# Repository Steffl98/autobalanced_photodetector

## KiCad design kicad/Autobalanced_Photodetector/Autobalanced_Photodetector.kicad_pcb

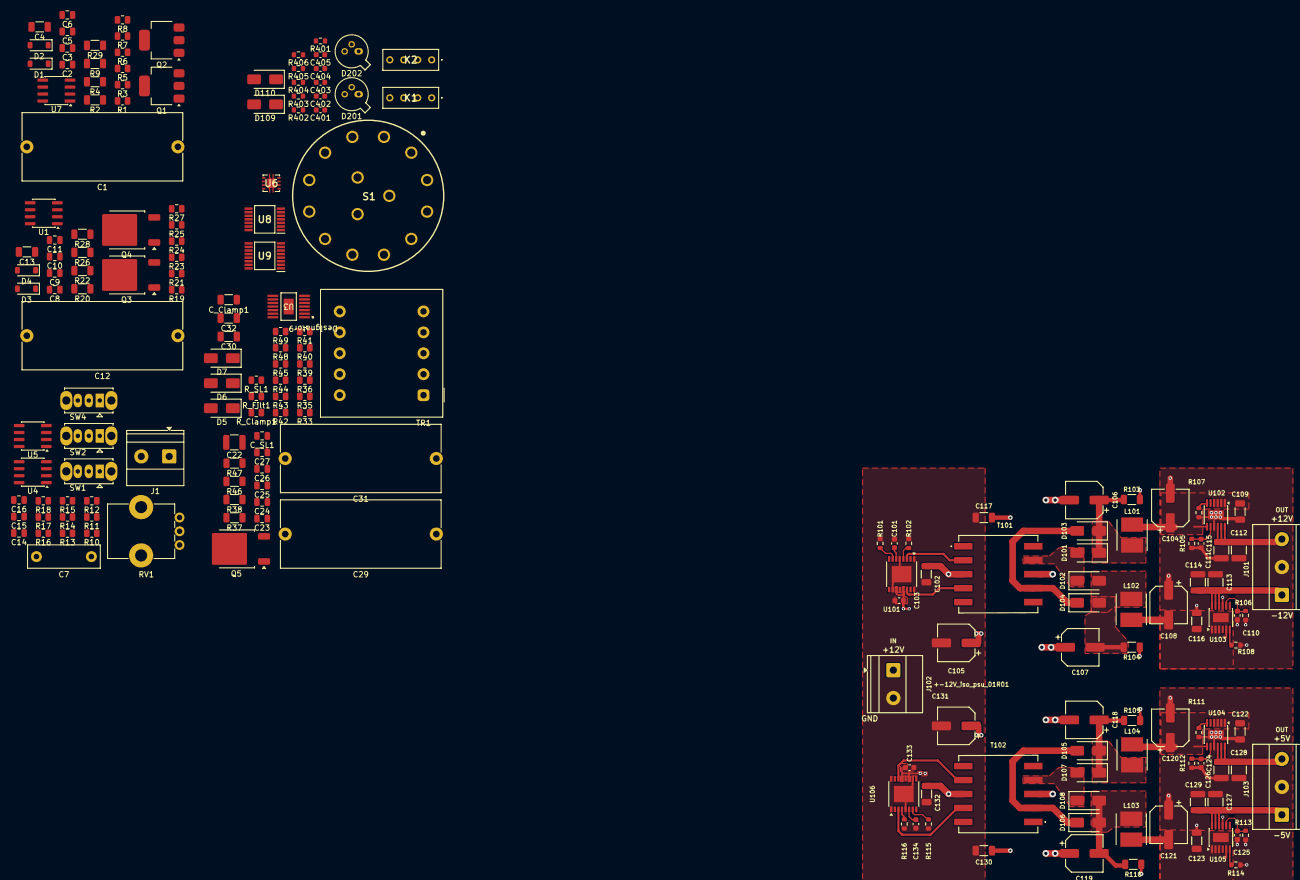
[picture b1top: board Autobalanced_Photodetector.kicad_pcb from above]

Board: 2 copper layers, 193 parts (0 on the bottom side), 117 nets.

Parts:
C1, C12, C29, C31: 3.3u; C_Rect_L29.0mm_W12.2mm_P27.50mm_MKT
C2, C11: 15n; C_0805_2012Metric
C3, C5, C6, C8, C9, C10, C14, C15, C16, C23, C24: 100n; C_0805_2012Metric
C4, C13, C30, C32: 10n; C_1206_3216Metric
C7: 1u; C_Rect_L13.0mm_W4.0mm_P10.00mm_FKS3_FKP3_MKS4
C22: 22u; C_1210_3225Metric
C25: 2.2u; C_0805_2012Metric
C26: 4.7u; C_0805_2012Metric
C27: 4.7n; C_0805_2012Metric
C101, C134: 680pF; C_0603_1608Metric
C102, C109, C116, C117, C122, C123, C130, C132: 4.7u; C_1206_3216Metric
C103, C133: 100nF; C_0603_1608Metric
C104, C108, C120, C121: 47uF; CP_Elec_6.3x5.8
C105, C106, C107, C118, C119, C131: 100uF; CP_Elec_6.3x7.7
C110, C115, C124, C125: 4.7uF; C_0603_1608Metric
C111, C112, C113, C114, C126, C127, C128, C129: 22uF; C_1210_3225Metric
C401: 10n; C_0603_1608Metric
C402: 7.5n; C_0603_1608Metric
C403: 470p; C_0603_1608Metric
C404: 10p; C_0603_1608Metric
C405: 100n; C_0603_1608Metric
C_Clamp1: 4.7n; C_1206_3216Metric
C_SL1: 100p; C_0805_2012Metric
D1, D2, D3, D4: MMSZ5242B-E3-08; D_SOD-123
D5: MER3DMA-AU_R2_006A1; D_SMA
D6, D7: STTH1R06A; D_SMA
D101, D102, D103, D104, D105, D106, D107, D108, D109, D110: STPS1L60A; D_SMA
D201, D202: Photodiode_TO18; TO-18-3_Window
J1: Conn_01x02; TerminalBlock_Phoenix_MKDS-1,5-2-5.08_1x02_P5.08mm_Horizont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
J101, J103: Screw_Terminal_01x03; TerminalBlock_Phoenix_MKDS-1,5-3-5.08_1x03_P5.08mm_Horizont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
J102: Screw_Terminal_01x02; TerminalBlock_Phoenix_MKDS-1,5-2-5.08_1x02_P5.08mm_Horizont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
K1, K2: 9012-12-10; 90121210
L101, L102, L103, L104: 33uH; L_TDK_VLS5030EX
Q1, Q2: STN1NK60Z; SOT-223
Q3, Q4: FQD2P40TM; TO-252-2
Q5: IPD5N25S3-430; TO-252-2
R1, R23, R43: 10; R_0805_2012Metric
R2, R9, R20, R22: 120k; R_1206_3216Metric
R3, R14, R16, R17, R18, R21: 10k; R_0805_2012Metric
R4, R26, R28, R29: 680k; R_1206_3216Metric
R5, R6, R7, R24, R25, R27: 47k; R_0805_2012Metric
R8, R10, R19, R35: 1k; R_0805_2012Metric
R11: 4.7k; R_0805_2012Metric
R12: 470k; R_0805_2012Metric
R13, R15, R44: 100k; R_0805_2012Metric
R33: 0.1; R_0805_2012Metric
R36, R49: 100; R_0805_2012Metric
R37, R38, R46, R47: 220k; R_1206_3216Metric
R39, R48: 1.8k; R_0805_2012Metric
R40: 680k; R_0805_2012Metric
R41: 120k; R_0805_2012Metric
R42: 20k; R_0805_2012Metric
R45: 150k; R_0805_2012Metric
R101, R102, R115, R116: 16.9k; R_0603_1608Metric
R103, R104, R109, R110: 5k; R_1206_3216Metric
R105, R106: 120k; R_0603_1608Metric
R107, R404: 1k; R_0603_1608Metric
R108: 24.9k; R_0603_1608Metric
R111: 1.5k; R_0603_1608Metric
R112, R113: 49.9k; R_0603_1608Metric
R114: 37.4k; R_0603_1608Metric
R401: 15.9k; R_0603_1608Metric
R402, R403: 100k; R_0603_1608Metric
R405, R406: 10k; R_0603_1608Metric
RV1: R_Potentiometer; Potentiometer_Bourns_PTV09A-1_Single_Vertical
R_Clamp1: 18k; R_0805_2012Metric
R_Filt1: 100; R_0805_2012Metric
R_SL1: 2200; R_0805_2012Metric
S1: CK1051
SW1, SW2, SW4: SW_SPDT; SW_Slide_SPDT_Straight_CK_OS102011MS2Q
T101, T102: CTX02-16076; CTX0216076
TR1: Wuerth 750311681C enter-Tapped; Transformer_Wuerth_750343373
U1, U4, U5, U7: OPA2992IDR; SOIC-8_3.9x4.9mm_P1.27mm
U3: LM5156HPWPR; PWP0014H-IPC_A
U6: OPA659IDRBT; OPA659_DRB
U8: OPA4192IPWR; SOP65P640X120-14N
U9: TMUX6136PWR; SOP65P640X120-16N
U101, U106: LT3439; TSSOP-16-1EP_4.4x5mm_P0.65mm
U102, U104: LT3045xMSE; MSOP-12-1EP_3x4.039mm_P0.65mm_EP1.651x2.845mm
U103, U105: LT3094xMSE; MSOP-12-1EP_3x4.039mm_P0.65mm_EP1.651x2.845mm

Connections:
/Flyback/HV_RAW_NEG: C29.2, C30.2, D7.2 (A), R20.1, R23.1, R46.1
/Flyback/HV_RAW_POS: C31.1, C32.1, D6.1 (K), R1.1, R9.1, R37.1
/HV_Regulator_Neg/HV_BIAS_NEG: C12.1, C13.1, D4.1 (K), D202.3 (A), Q4.3 (S), R28.1
/HV_Regulator_Neg/V_REF_NEG: R17.2, R25.2, U5.7
/HV_Regulator_Pos/HV_BIAS_POS: C1.1, C4.1, D1.2 (A), D201.1 (K), Q1.3 (S), R4.1
/HV_Regulator_Pos/V_REF_POS: R6.2, R16.2, U5.1
/Photodetector/AB_EN: R405.1, S1.12, U9.1 (SEL1)
/Photodetector/PI_RESET: R406.1, S1.9, S1.10, S1.11, U9.9 (SEL2)
/Photodetector/PI_SUM: C404.1, R402.2, R403.1, U8.9 (-_IN_C), U9.11 (D2)
/Photodetector/RLY_MINUS: D110.1 (K), K2.2, S1.6, S1.7, S1.8
/Photodetector/RLY_PLUS: D109.1 (K), K1.2, S1.1, S1.3, S1.4
/Photodetector/VPI: C402.2, C403.2, C404.2, U8.8 (OUT_C), U9.2 (S1A), U9.10 (S2A)
/Photodetector/V_TRIM: SW4.1 (A), U8.13 (-_IN_D), U8.14 (OUT_D)
/Reference_Control/V_REF_SRC: R14.1, R18.1, U4.6 (-), U4.7
AGND: C1.2, C3.2, C4.2, C5.2, C7.2, C9.2, C10.2, C12.2, C13.2, C14.2, C15.2, C22.2, C23.1, C24.2, C25.1, C26.1, C29.1, C30.1, C31.2, C32.2, C104.2, C106.2, C107.1, C108.1, C109.2, C110.1, C111.2, C112.2, C113.2, C114.2, C115.2, C116.1, C117.2, C118.2, C119.1, C120.2, C121.1, C122.2, C123.1, C124.2, C125.1, C126.2, C127.2, C128.2, C129.2, C130.2, C401.2, C405.2, C_SL1.1, D201.2 (CASE), D202.2 (CASE), J1.2, J101.2, J103.2, R5.2, R10.2, R15.1, R27.2, R33.2, R35.1, R36.2, R40.2, R42.2, R45.1, R49.2, R103.2, R104.1, R105.2, R106.1, R107.2, R108.1, R109.2, R110.1, R111.2, R112.2, R113.1, R114.1, R405.2, R406.2, SW4.3 (C), T101.8 (SEC_1-), T102.3 (PRI_1-), TR1.5, TR1.7, U3.5 (PGND), U3.6 (AGND), U3.15 (EP), U5.5 (+), U6.3 (+), U8.10 (+IN_C), U9.6 (GND), U102.9 (GND), U102.13 (GND), U103.9 (GND), U104.9 (GND), U104.13 (GND), U105.9 (GND)
unnamed: C2.1, R7.2
unnamed: C11.1, R24.2
unnamed: C27.1, R40.1
unnamed: C402.1, C403.1, R403.2
unnamed: C_SL1.2, R_Filt1.1, R_SL1.2
unnamed: D1.1 (K), Q1.1 (G), Q2.2 (D), R2.2
unnamed: D2.2 (A), Q2.3 (S), R3.1, U7.6 (-)
unnamed: D2.1 (K), Q2.1 (G), R8.2
unnamed: D3.2 (A), Q3.1 (G), R19.2
unnamed: D3.1 (K), Q3.3 (S), R21.1, U1.6 (-)
unnamed: D4.2 (A), Q3.2 (D), Q4.1 (G), R22.2
unnamed: D5.2 (A), Q5.1 (D), TR1.1
unnamed: C_Clamp1.2, D5.1 (K), R_Clamp1.1
unnamed: D6.2 (A), TR1.4
unnamed: D7.1 (K), TR1.6
unnamed: D101.2 (A), D102.1 (K), T101.9 (SEC_1+)
unnamed: C106.1, D101.1 (K), D103.1 (K), L101.1, R103.1
unnamed: C107.2, D102.2 (A), D104.2 (A), L102.1, R104.2
unnamed: D103.2 (A), D104.1 (K), T101.7 (SEC_2-)
unnamed: D105.2 (A), D106.1 (K), T102.2 (PRI_1+)
unnamed: C118.1, D105.1 (K), D107.1 (K), L104.1, R109.1
unnamed: C119.2, D106.2 (A), D108.2 (A), L103.1, R110.2
unnamed: D107.2 (A), D108.1 (K), T102.4 (PRI_2-)
unnamed: D201.3 (A), K1.1
unnamed: D202.1 (K), K2.4
unnamed: J1.1, SW1.3 (C)
unnamed: Q1.2 (D), R1.2
unnamed: Q4.2 (D), R23.2
unnamed: Q5.2 (G), R43.2, R44.1
unnamed: Q5.3 (S), R33.1, R44.2, R_Filt1.2
unnamed: R2.1, R9.2
unnamed: R8.1, U7.7
unnamed: R10.1, RV1.3
unnamed: R11.2, RV1.1
unnamed: R19.1, U1.7
unnamed: R20.2, R22.1
unnamed: R26.1, R28.2
unnamed: R4.2, R29.1
unnamed: R36.1, R39.2
unnamed: R37.2, R38.1
unnamed: R46.2, R47.1
unnamed: R47.2, R48.1
unnamed: R48.2, R49.1
unnamed: RV1.2, SW1.1 (A)
unnamed: SW1.2 (B), U4.3 (+)
unnamed: SW2.1 (A), U4.1, U4.2 (-)
unnamed: R12.1, SW2.2 (B)
unnamed: R13.1, SW4.2 (B)
unnamed: T101.2 (PRI_1+), U101.3 (COLA)
unnamed: T101.4 (PRI_2-), U101.14 (COLB)
unnamed: T102.9 (SEC_1+), U106.3 (COLA)
unnamed: T102.7 (SEC_2-), U106.14 (COLB)
unnamed: R26.2, R27.1, U1.3 (+)
unnamed: C11.2, R25.1, U1.2 (-)
unnamed: R24.1, U1.1, U1.5 (+)
unnamed: C27.2, U3.8 (COMP)
unnamed: R_SL1.1, U3.7 (CS)
unnamed: R35.2, U3.9 (DITHOFF)
unnamed: R41.2, R42.1, U3.14 (EN_UVLO_SYNC)
unnamed: R38.2, R39.1, U3.10 (FB)
unnamed: R43.1, U3.4 (GATE)
unnamed: R45.2, U3.12 (RT)
unnamed: C26.2, U3.11 (SS)
unnamed: C25.2, U3.3 (VCC)
unnamed: C7.1, R12.2, U4.5 (+)
unnamed: R13.2, R14.2, U5.3 (+)
unnamed: R15.2, R16.1, U5.2 (-)
unnamed: R17.1, R18.2, U5.6 (-)
unnamed: K1.4, K2.1, U6.2 (-)
unnamed: R5.1, R29.2, U7.3 (+)
unnamed: C2.2, R6.1, U7.2 (-)
unnamed: R7.1, U7.1, U7.5 (+)
unnamed: C401.1, R401.2, U8.5 (+_IN_B)
unnamed: C405.1, R404.2, U8.12 (+_IN_D)
unnamed: R401.1, U8.1 (OUT_A), U8.2 (-IN_A)
unnamed: R402.1, U8.6 (-_IN_B), U8.7 (OUT_B)
unnamed: R404.1, U9.3 (D1)
unnamed: C101.1, U101.6 (Ct)
unnamed: R102.2, U101.4 (Rsl)
unnamed: R101.2, U101.7 (Rt)
unnamed: C104.1, C109.1, L101.2, U102.1 (IN), U102.2 (IN), U102.3 (IN), U102.4 (EN/UV), U102.7 (PGFB)
unnamed: R107.1, U102.6 (ILIM)
unnamed: C115.1, R105.1, U102.8 (SET)
unnamed: C108.2, C116.2, L102.2, U103.1 (IN), U103.2 (IN), U103.3 (EN/UV), U103.5 (PGFB), U103.13 (IN)
unnamed: R108.2, U103.6 (ILIM)
unnamed: C110.2, R106.2, U103.8 (SET)
unnamed: C120.1, C122.1, L104.2, U104.1 (IN), U104.2 (IN), U104.3 (IN), U104.4 (EN/UV), U104.7 (PGFB)
unnamed: R111.1, U104.6 (ILIM)
unnamed: C124.1, R112.1, U104.8 (SET)
unnamed: C121.2, C123.2, L103.2, U105.1 (IN), U105.2 (IN), U105.3 (EN/UV), U105.5 (PGFB), U105.13 (IN)
unnamed: R114.2, U105.6 (ILIM)
unnamed: C125.2, R113.2, U105.8 (SET)
unnamed: C134.1, U106.6 (Ct)
unnamed: R116.2, U106.4 (Rsl)
unnamed: R115.2, U106.7 (Rt)
PGND: C101.2, C102.2, C103.2, C105.2, C117.1, C130.1, C131.2, C132.2, C133.2, C134.2, D109.2 (A), D110.2 (A), J102.2, K1.3, K2.3, R101.1, R102.1, R115.1, R116.1, U101.1 (PGND), U101.5 (SYNC), U101.10 (GND), U101.16 (PGND), U101.17 (PADGND), U106.1 (PGND), U106.5 (SYNC), U106.10 (GND), U106.16 (PGND), U106.17 (PADGND)
TIA_OUT: U6.6 (OUT), U8.3 (+_IN_A)
VCC_5V: C126.1, C128.1, J103.3, S1.15 (C), U6.7 (V+), U104.10 (OUTS), U104.11 (OUT), U104.12 (OUT)
VCC_12V: C5.1, C6.2, C8.2, C9.1, C14.1, C16.2, C111.1, C112.1, J101.3, R11.1, R21.2, U1.8 (V+), U4.8 (V+), U5.8 (V+), U7.8 (V+), U8.4 (V+), U9.13 (VDD), U102.10 (OUTS), U102.11 (OUT), U102.12 (OUT)
VEE_5V: C127.1, C129.1, J103.1, U6.4 (V-), U6.9 (EP), U105.10 (OUTS), U105.11 (OUT), U105.12 (OUT)
VEE_12V: C3.1, C6.1, C8.1, C10.1, C15.1, C16.1, C113.1, C114.1, J101.1, R3.2, SW2.3 (C), U1.4 (V-), U4.4 (V-), U5.4 (V-), U7.4 (V-), U8.11 (V-), U9.4 (S1B), U9.5 (VSS), U103.10 (OUTS), U103.11 (OUT), U103.12 (OUT)
VFLY_12V: C22.1, C23.2, C24.1, C102.1, C103.1, C105.1, C131.1, C132.1, C133.1, C_Clamp1.1, J102.1, R41.1, R_Clamp1.2, S1.13 (A), S1.14 (B), T101.3 (PRI_1-), T102.8 (SEC_1-), TR1.3, U3.1 (BIAS), U101.11 (~SHDN), U101.13 (VIN), U106.11 (~SHDN), U106.13 (VIN)
